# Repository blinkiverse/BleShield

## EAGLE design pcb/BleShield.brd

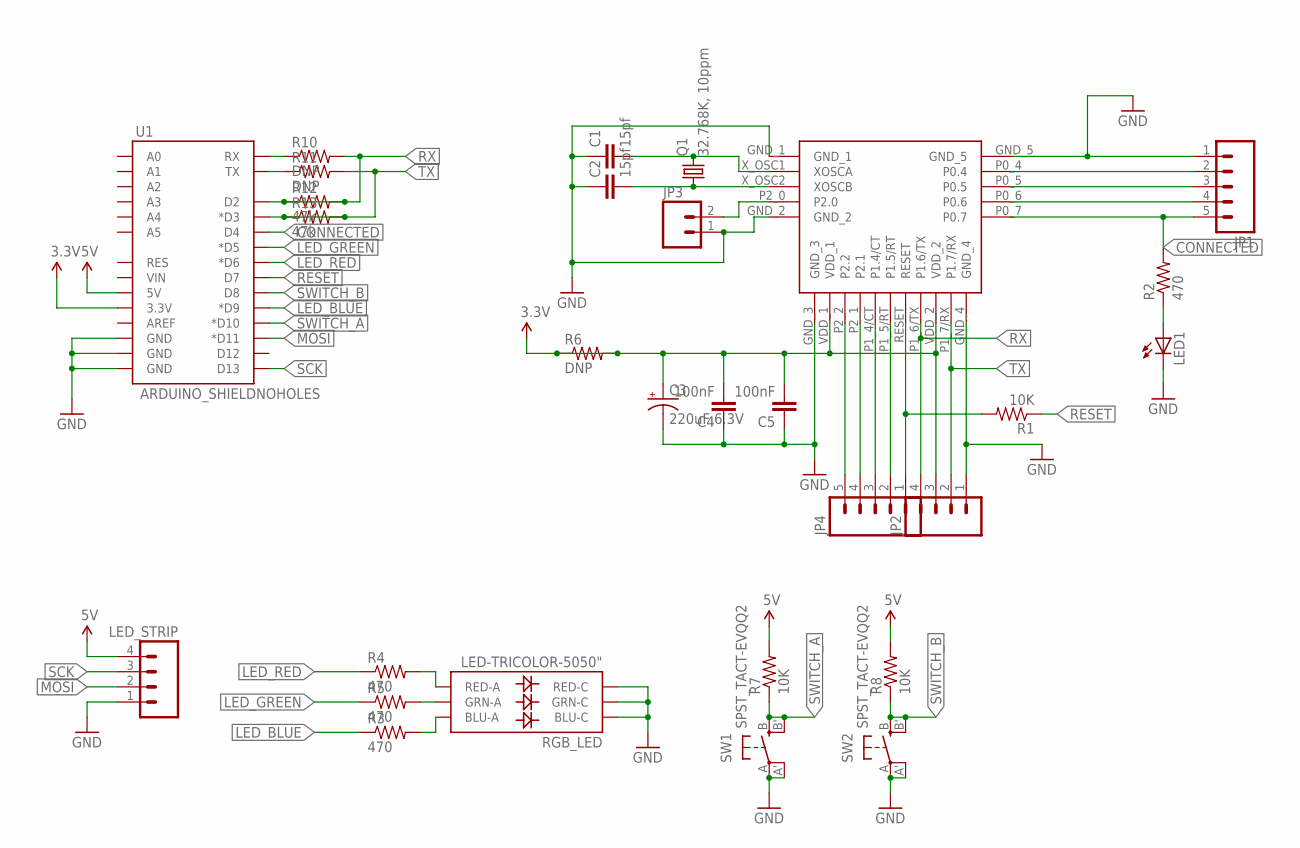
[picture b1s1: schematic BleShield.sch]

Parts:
C1, C2: 15pf; 0805
C3: 220uF 6.3V; C/6032-28R
C4, C5: 100nF; 0805
JP1, JP4: M051.27MM; 1X05-1.27MM
JP2: M041.27MM; 1X04-1.27MM
JP3: M02; 1X02-1.27MM
LED1: LEDCHIPLED_0805; CHIPLED_0805
LED_STRIP: M04PTH; 1X04
Q1: 32.768K, 10ppm; CRYSTAL_3215
R1, R7, R8: 10K; 0805
R2, R3, R4, R5: 470; 0805
R6, R10, R11: DNP; 0805
R12, R13: 47k; 0805
RGB_LED: LED-TRICOLOR-5050"; LED-TRICOLOR-5050-FIXED
SW1, SW2: SPST_TACT-EVQQ2; EVQ-Q2
U1: ARDUINO_SHIELDNOHOLES; DUEMILANOVE_SHIELD_NOHOLES
U$1: BG213L; BG312L

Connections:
3.3V: C3.+, C4.2, C5.2, JP2.3, R6.1, R6.2, U1.3.3V, U$1.VDD_1, U$1.VDD_2
5V: LED_STRIP.4, R7.2, R8.2, U1.5V
CONNECTED: JP1.5, R2.2, U1.D4, U$1.P0_7 (P0.7)
GND: C1.1, C2.1, C3.-, C4.1, C5.1, JP1.1, JP2.1, JP3.1, LED1.C, LED_STRIP.1, RGB_LED.1 (BLU-C), RGB_LED.2 (RED-C), RGB_LED.3 (GRN-C), SW1.A, SW1.A' (P1), SW2.A, SW2.A' (P1), U1.GND@0 (GND), U1.GND@1 (GND), U1.GND@2 (GND), U$1.GND_1, U$1.GND_2, U$1.GND_3, U$1.GND_4, U$1.GND_5
LED_BLUE: R3.1, U1.D9 (*D9)
LED_GREEN: R5.1, U1.D5 (*D5)
LED_RED: R4.1, U1.D6 (*D6)
MOSI: LED_STRIP.2, U1.D11 (*D11)
unnamed: JP4.1, R1.2, U$1.RESET
unnamed: R3.2, RGB_LED.6 (BLU-A)
unnamed: C1.2, Q1.P$2 (2), U$1.X_OSC1 (XOSCA)
unnamed: C2.2, Q1.P$1 (1), U$1.X_OSC2 (XOSCB)
unnamed: R5.2, RGB_LED.4 (GRN-A)
unnamed: R4.2, RGB_LED.5 (RED-A)
unnamed: LED1.A, R2.1
unnamed: JP4.5, U$1.P2_2 (P2.2)
unnamed: R10.1, U1.RX
unnamed: R11.1, U1.TX
unnamed: JP4.4, U$1.P2_1 (P2.1)
unnamed: JP4.3, U$1.P1_4/CT (P1.4/CT)
unnamed: JP4.2, U$1.P1_5/RT (P1.5/RT)
unnamed: JP1.2, U$1.P0_4 (P0.4)
unnamed: JP1.3, U$1.P0_5 (P0.5)
unnamed: JP1.4, U$1.P0_6 (P0.6)
unnamed: JP3.2, U$1.P2_0 (P2.0)
RESET: R1.1, U1.D7
RX: JP2.4, R10.2, R12.1, R12.2, U1.D2, U$1.P1_6/TX (P1.6/TX)
SCK: LED_STRIP.3, U1.D13
SWITCH_A: R7.1, SW1.B (S), SW1.B' (S1), U1.D10 (*D10)
SWITCH_B: R8.1, SW2.B (S), SW2.B' (S1), U1.D8
TX: JP2.2, R11.2, R13.1, R13.2, U1.D3 (*D3), U$1.P1_7/RX (P1.7/RX)

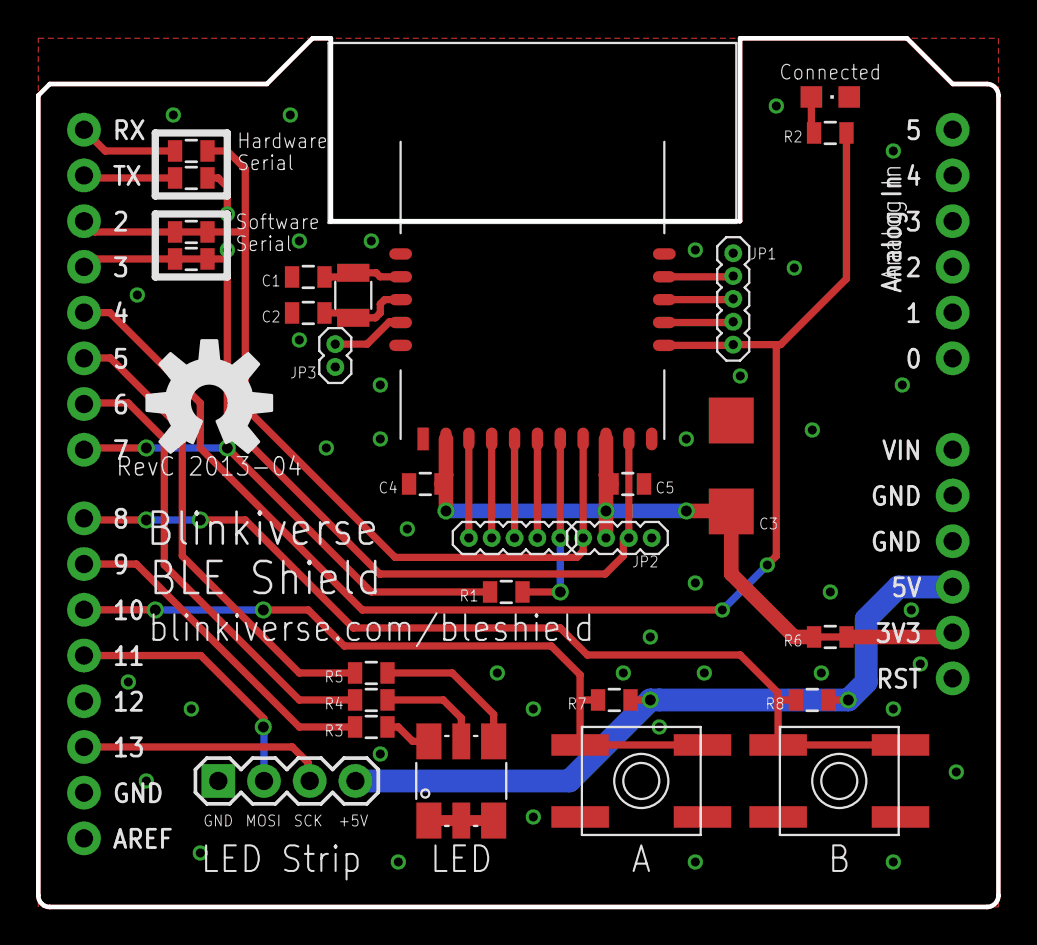
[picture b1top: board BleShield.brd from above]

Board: 2 copper layers, 53.3 x 48.3 mm, 30 parts (0 on the bottom side), 31 nets.

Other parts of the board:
U$7: OSHW-LOGO-L

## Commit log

2013-04-11 Put the 47k resistors in for the pick&place machine

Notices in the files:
parts and their libraries:
SparkFun: Licensing: CC v3.0 Share-Alike You are welcome to use this library for commercial purposes.
